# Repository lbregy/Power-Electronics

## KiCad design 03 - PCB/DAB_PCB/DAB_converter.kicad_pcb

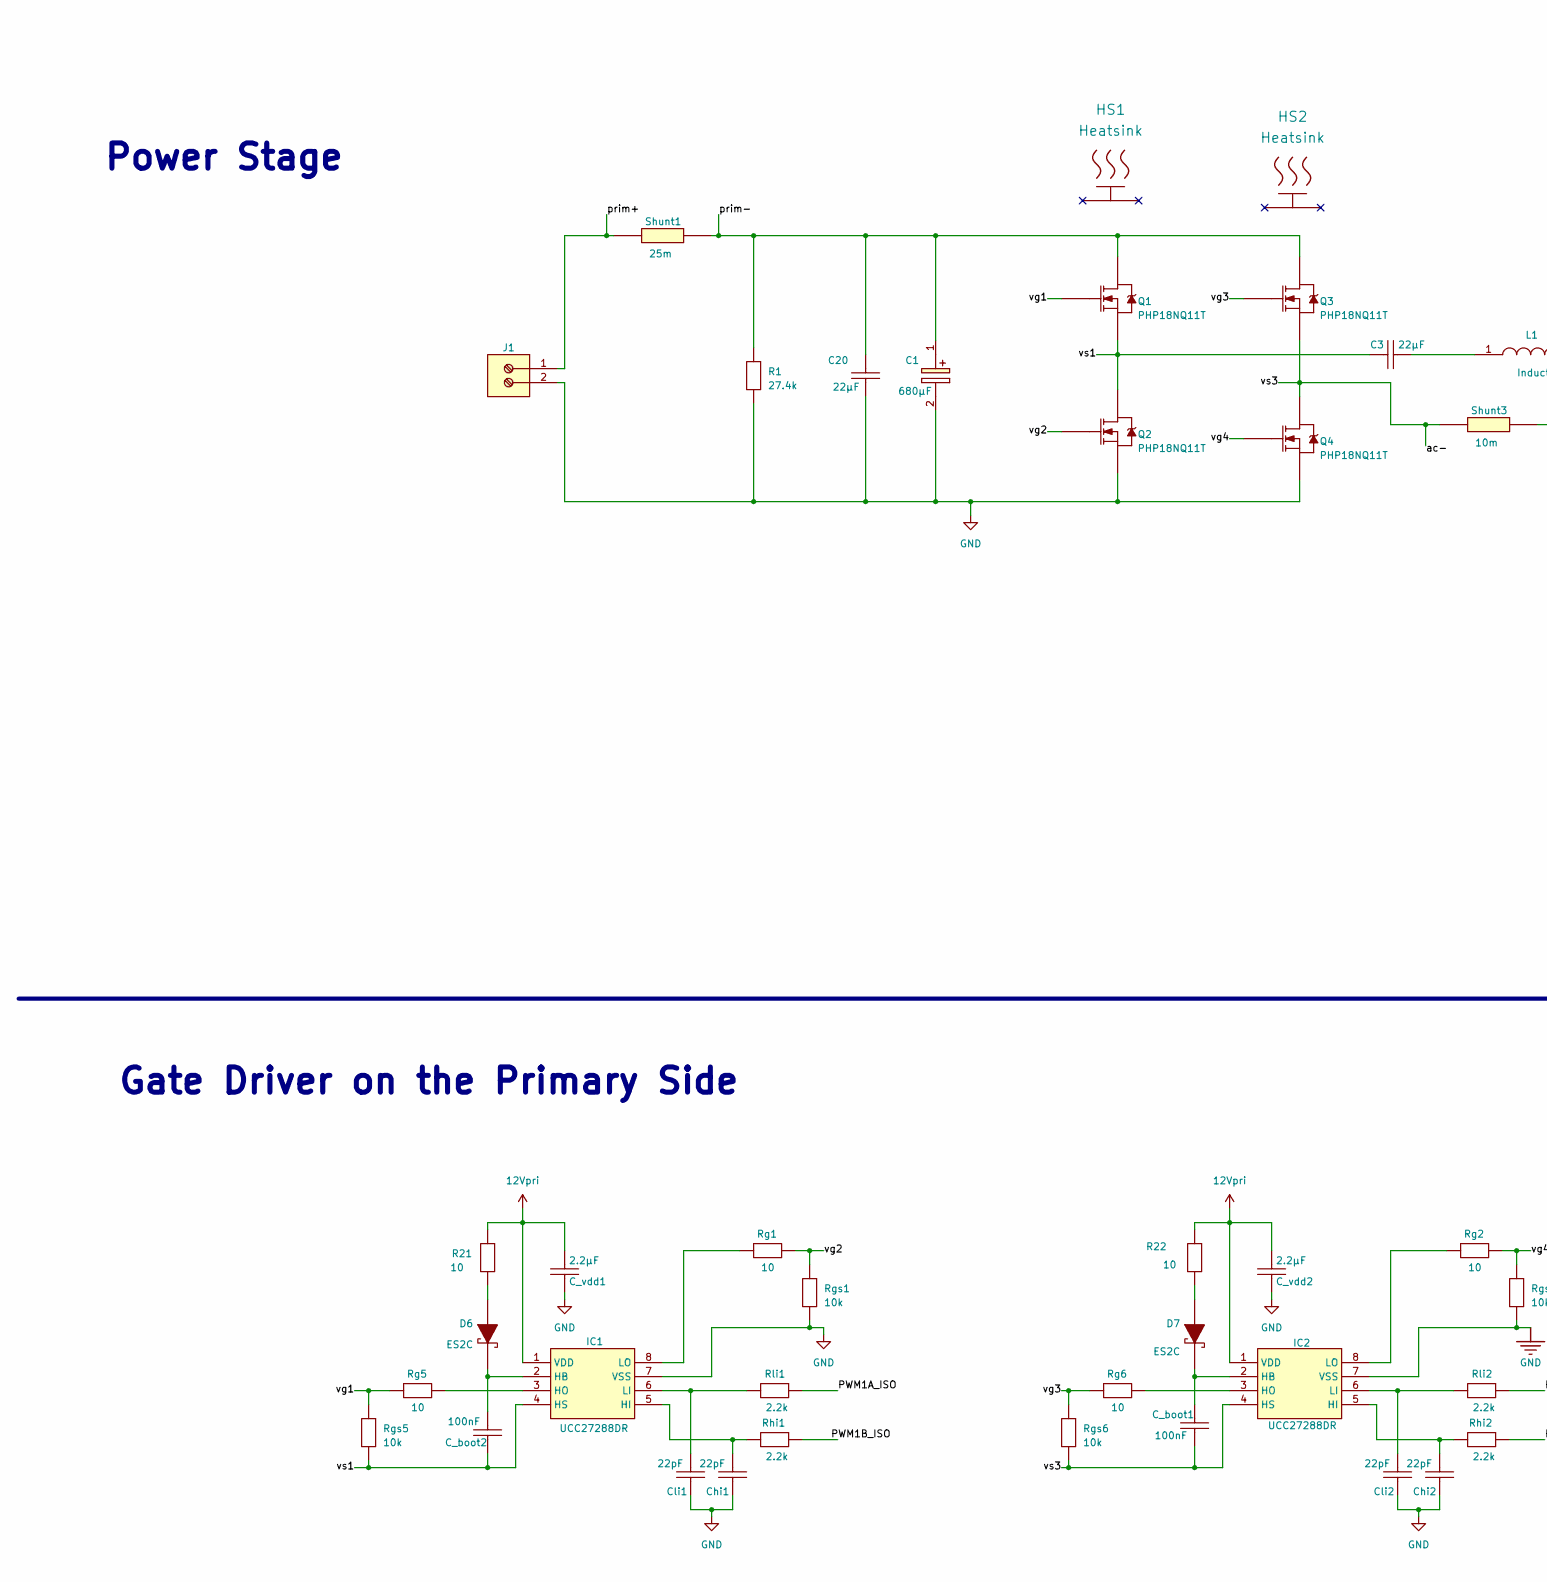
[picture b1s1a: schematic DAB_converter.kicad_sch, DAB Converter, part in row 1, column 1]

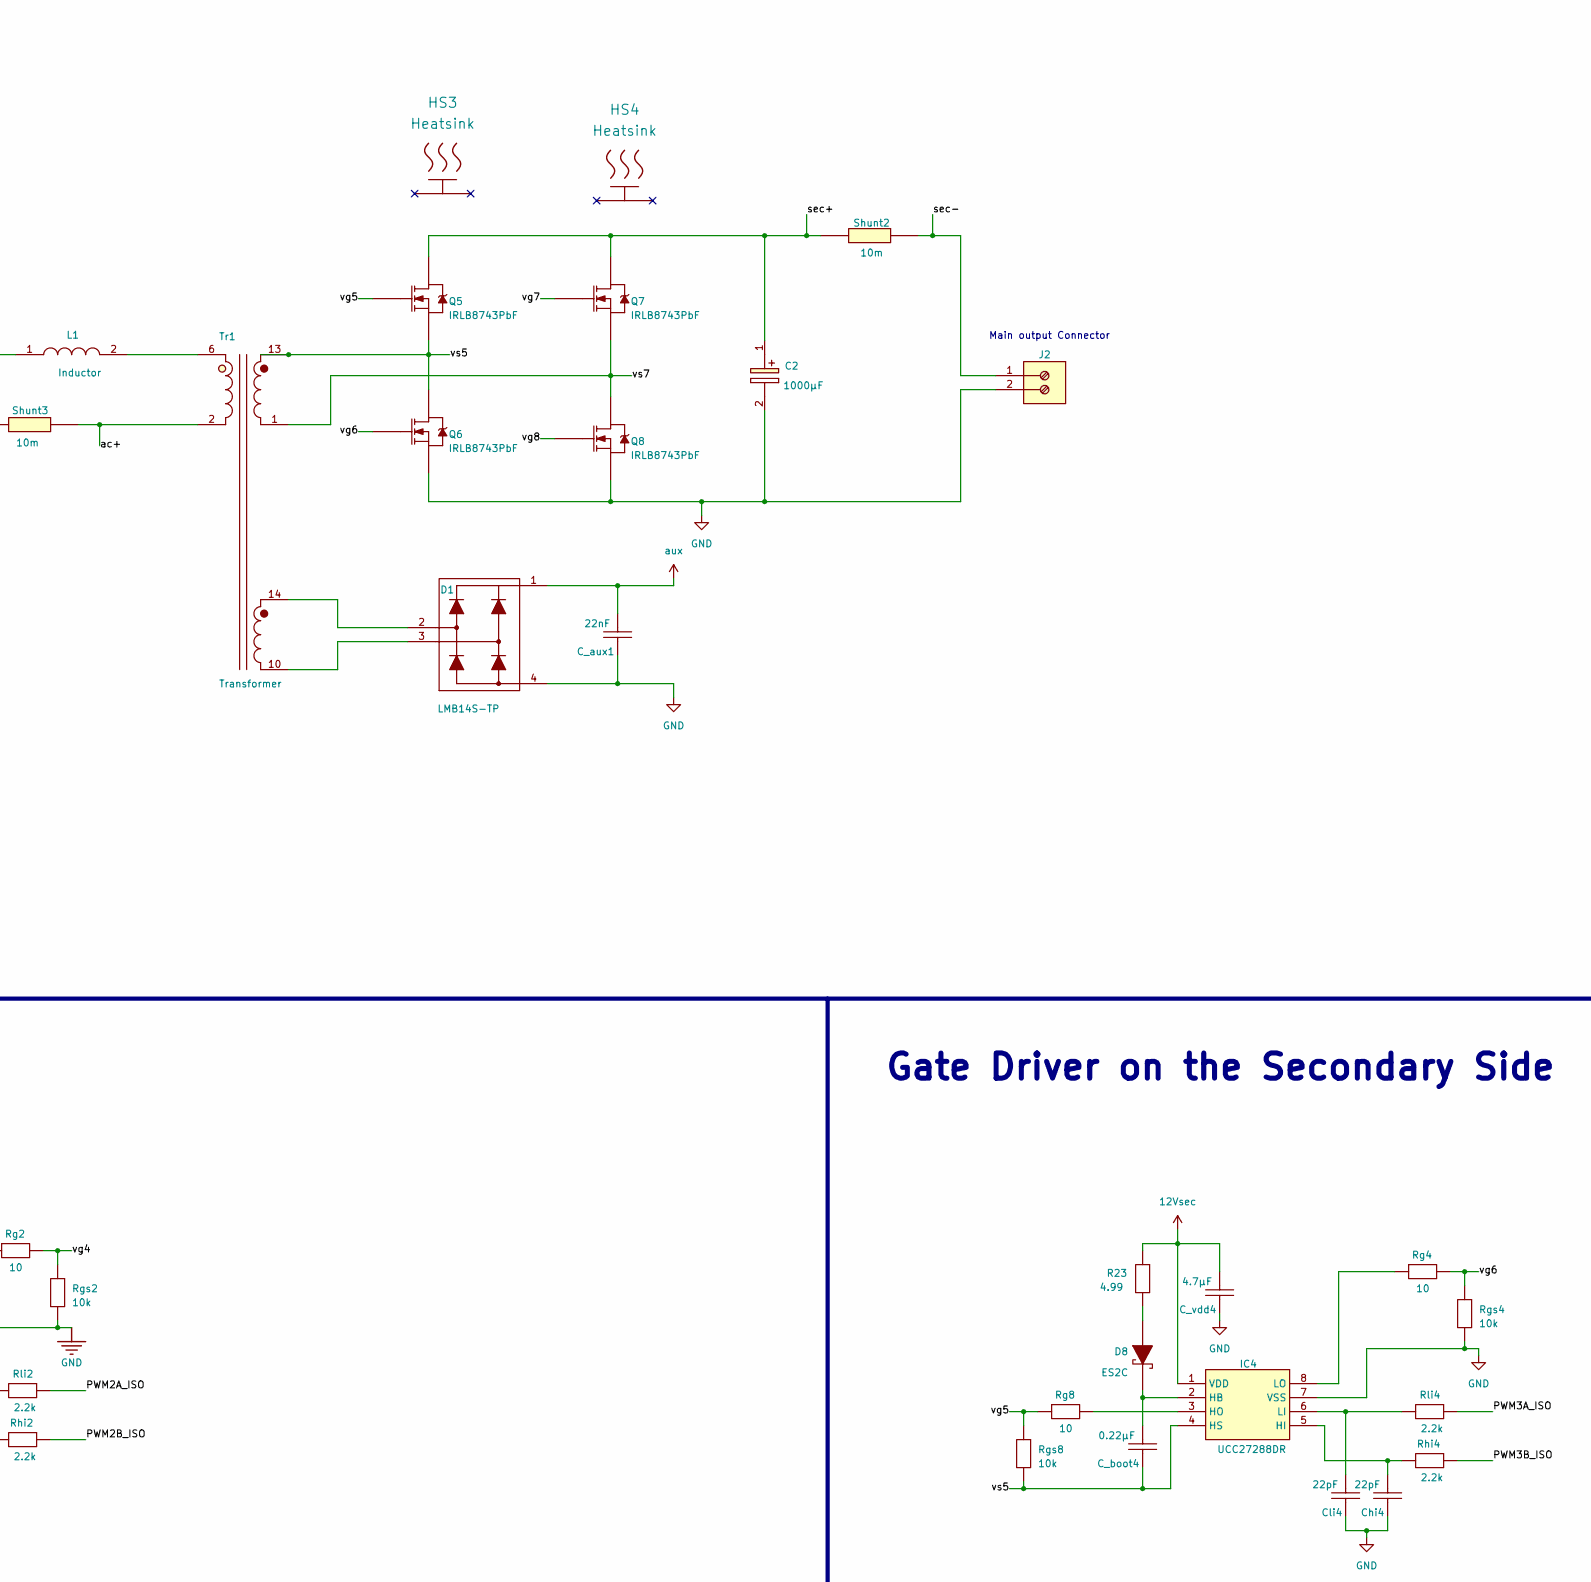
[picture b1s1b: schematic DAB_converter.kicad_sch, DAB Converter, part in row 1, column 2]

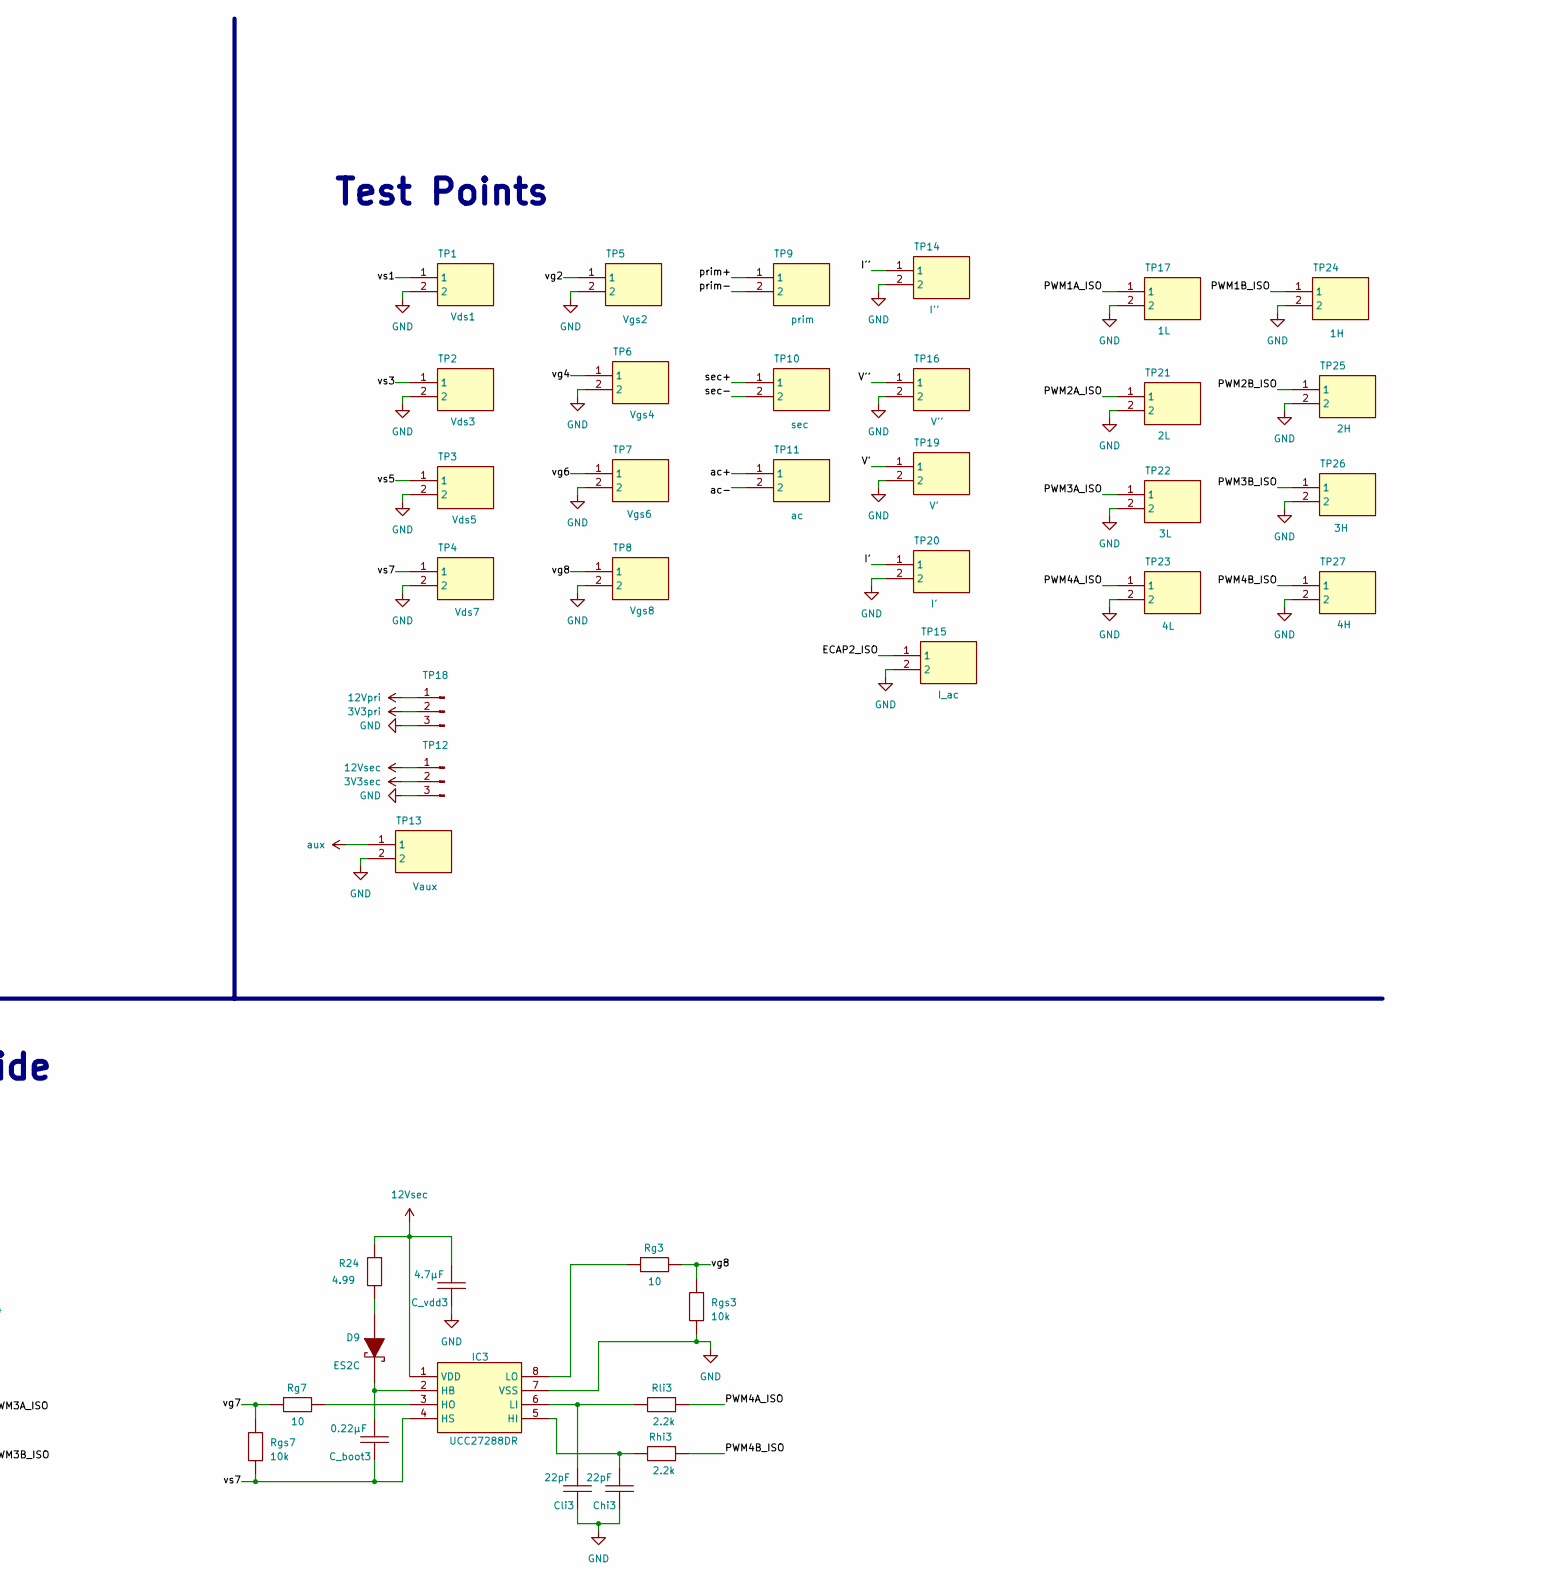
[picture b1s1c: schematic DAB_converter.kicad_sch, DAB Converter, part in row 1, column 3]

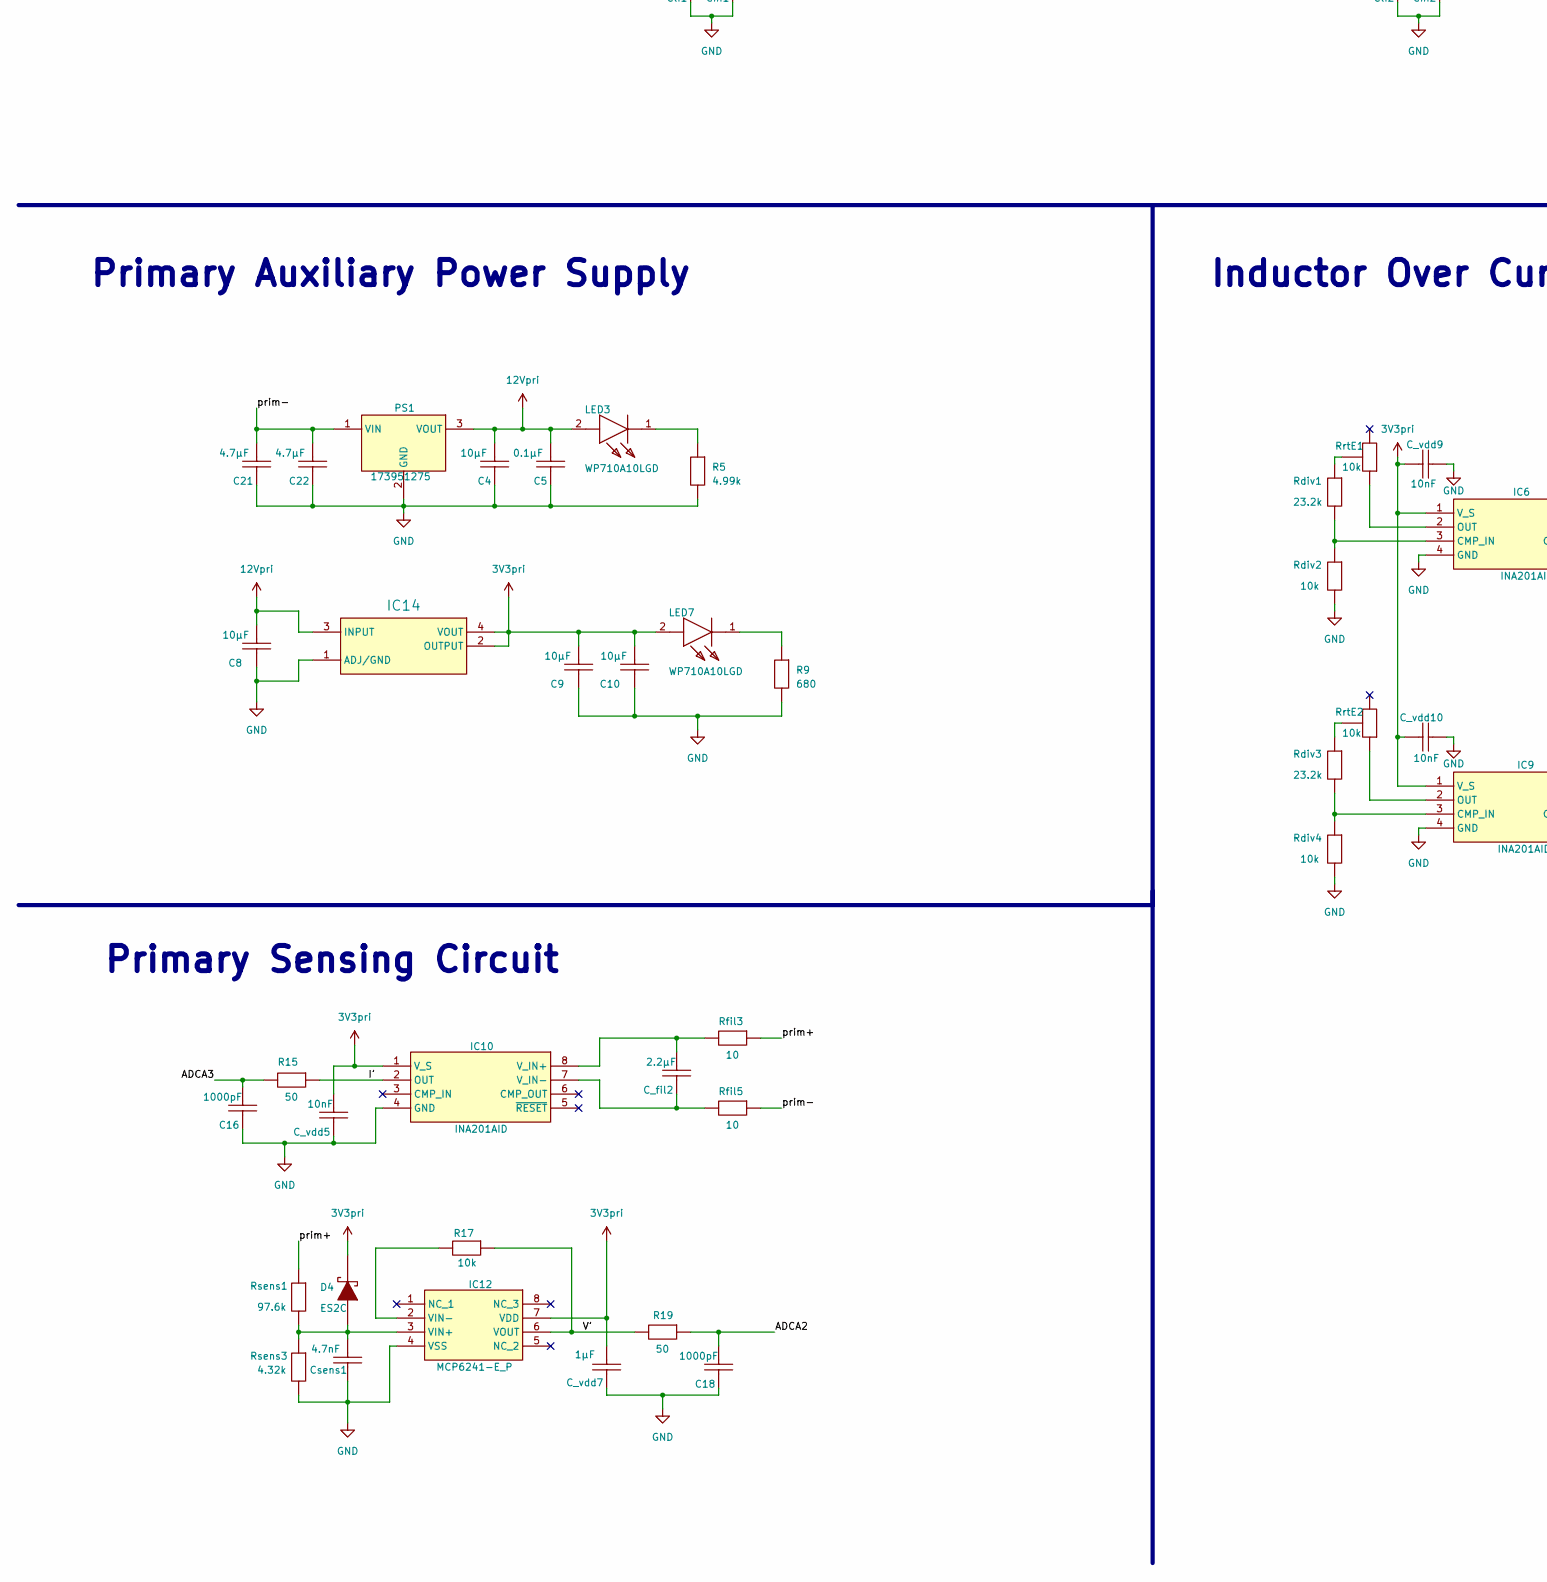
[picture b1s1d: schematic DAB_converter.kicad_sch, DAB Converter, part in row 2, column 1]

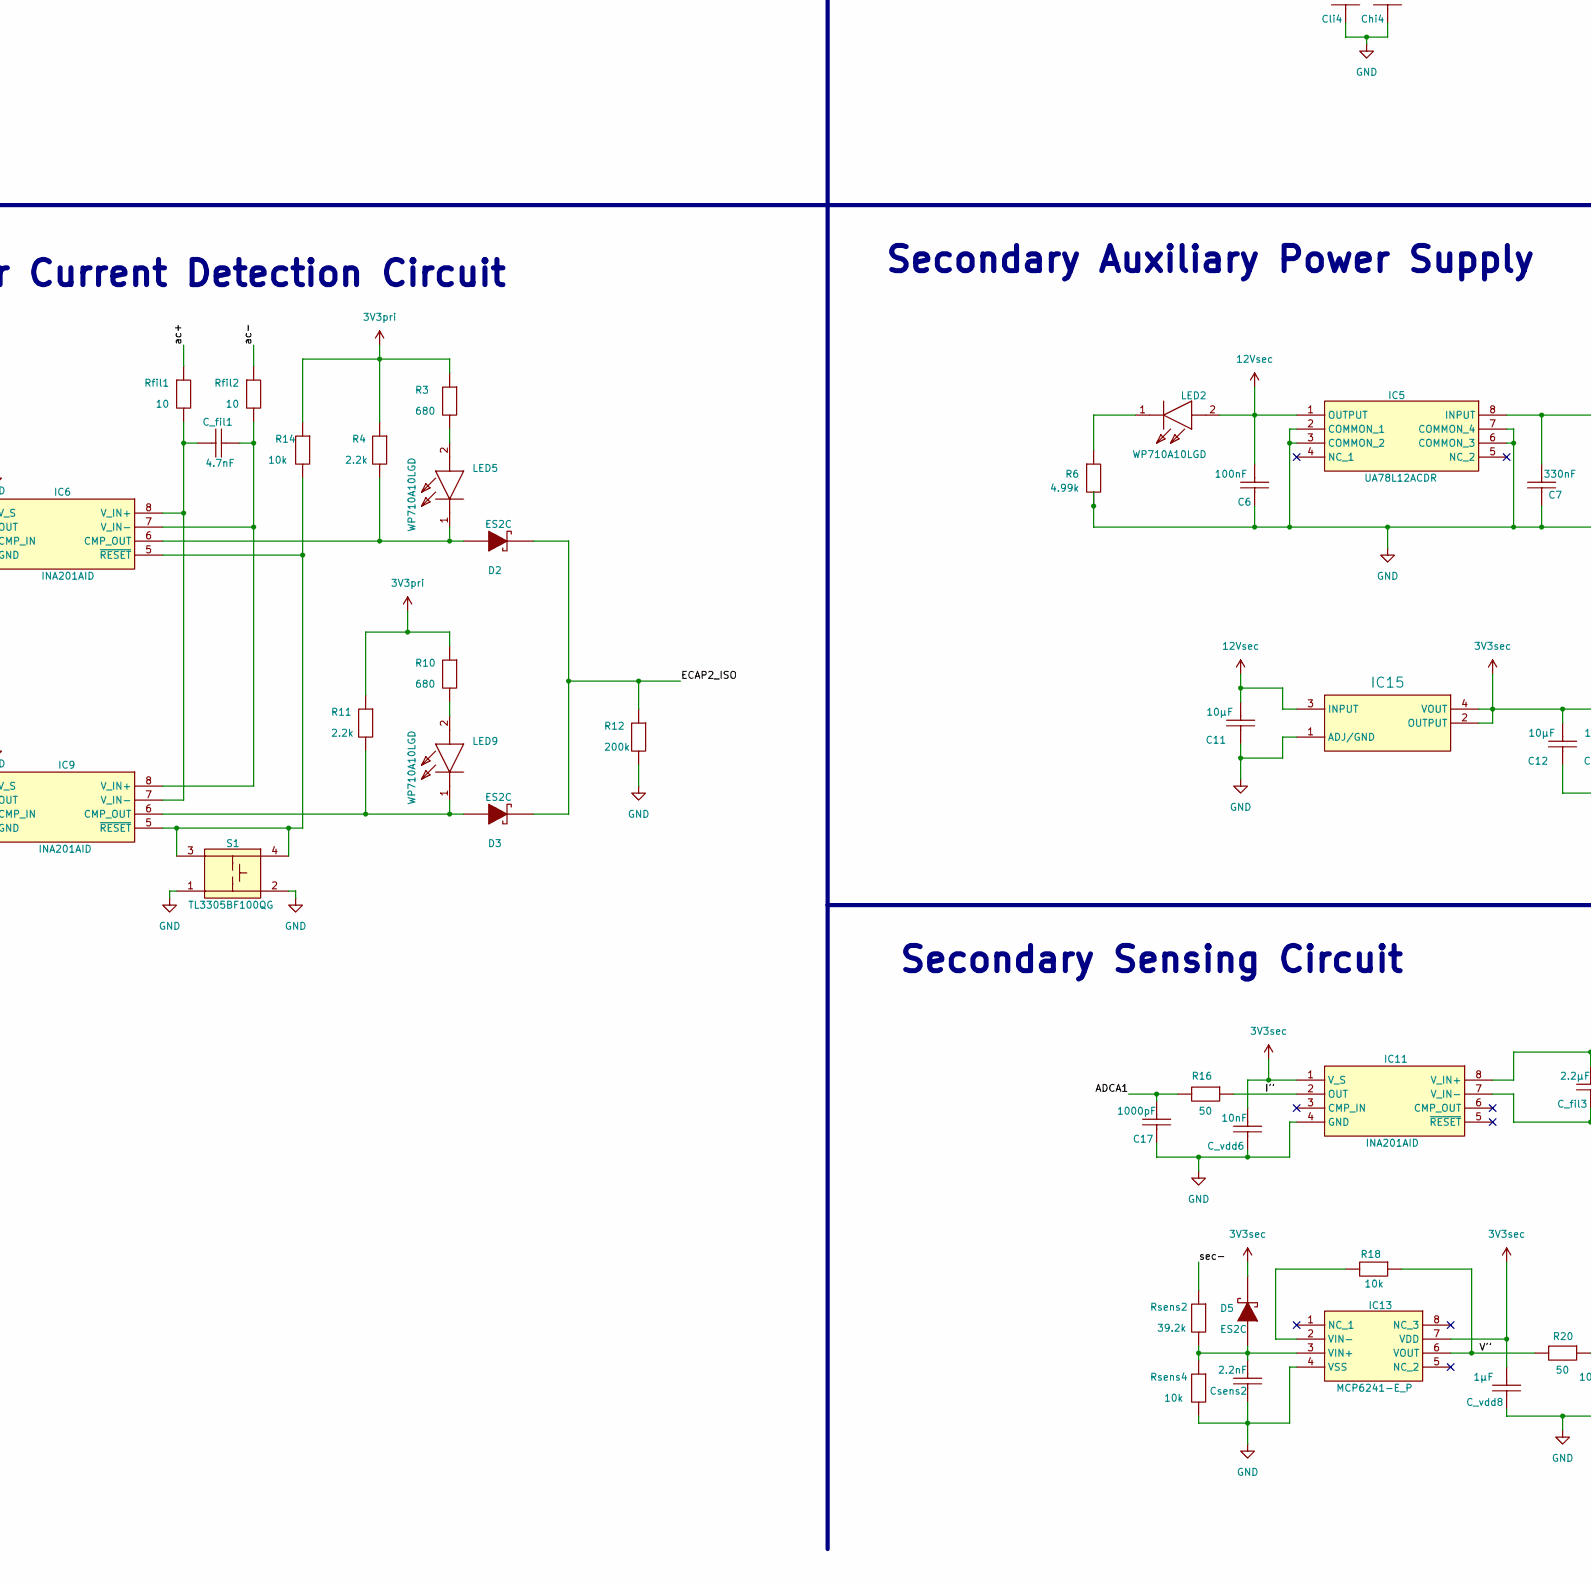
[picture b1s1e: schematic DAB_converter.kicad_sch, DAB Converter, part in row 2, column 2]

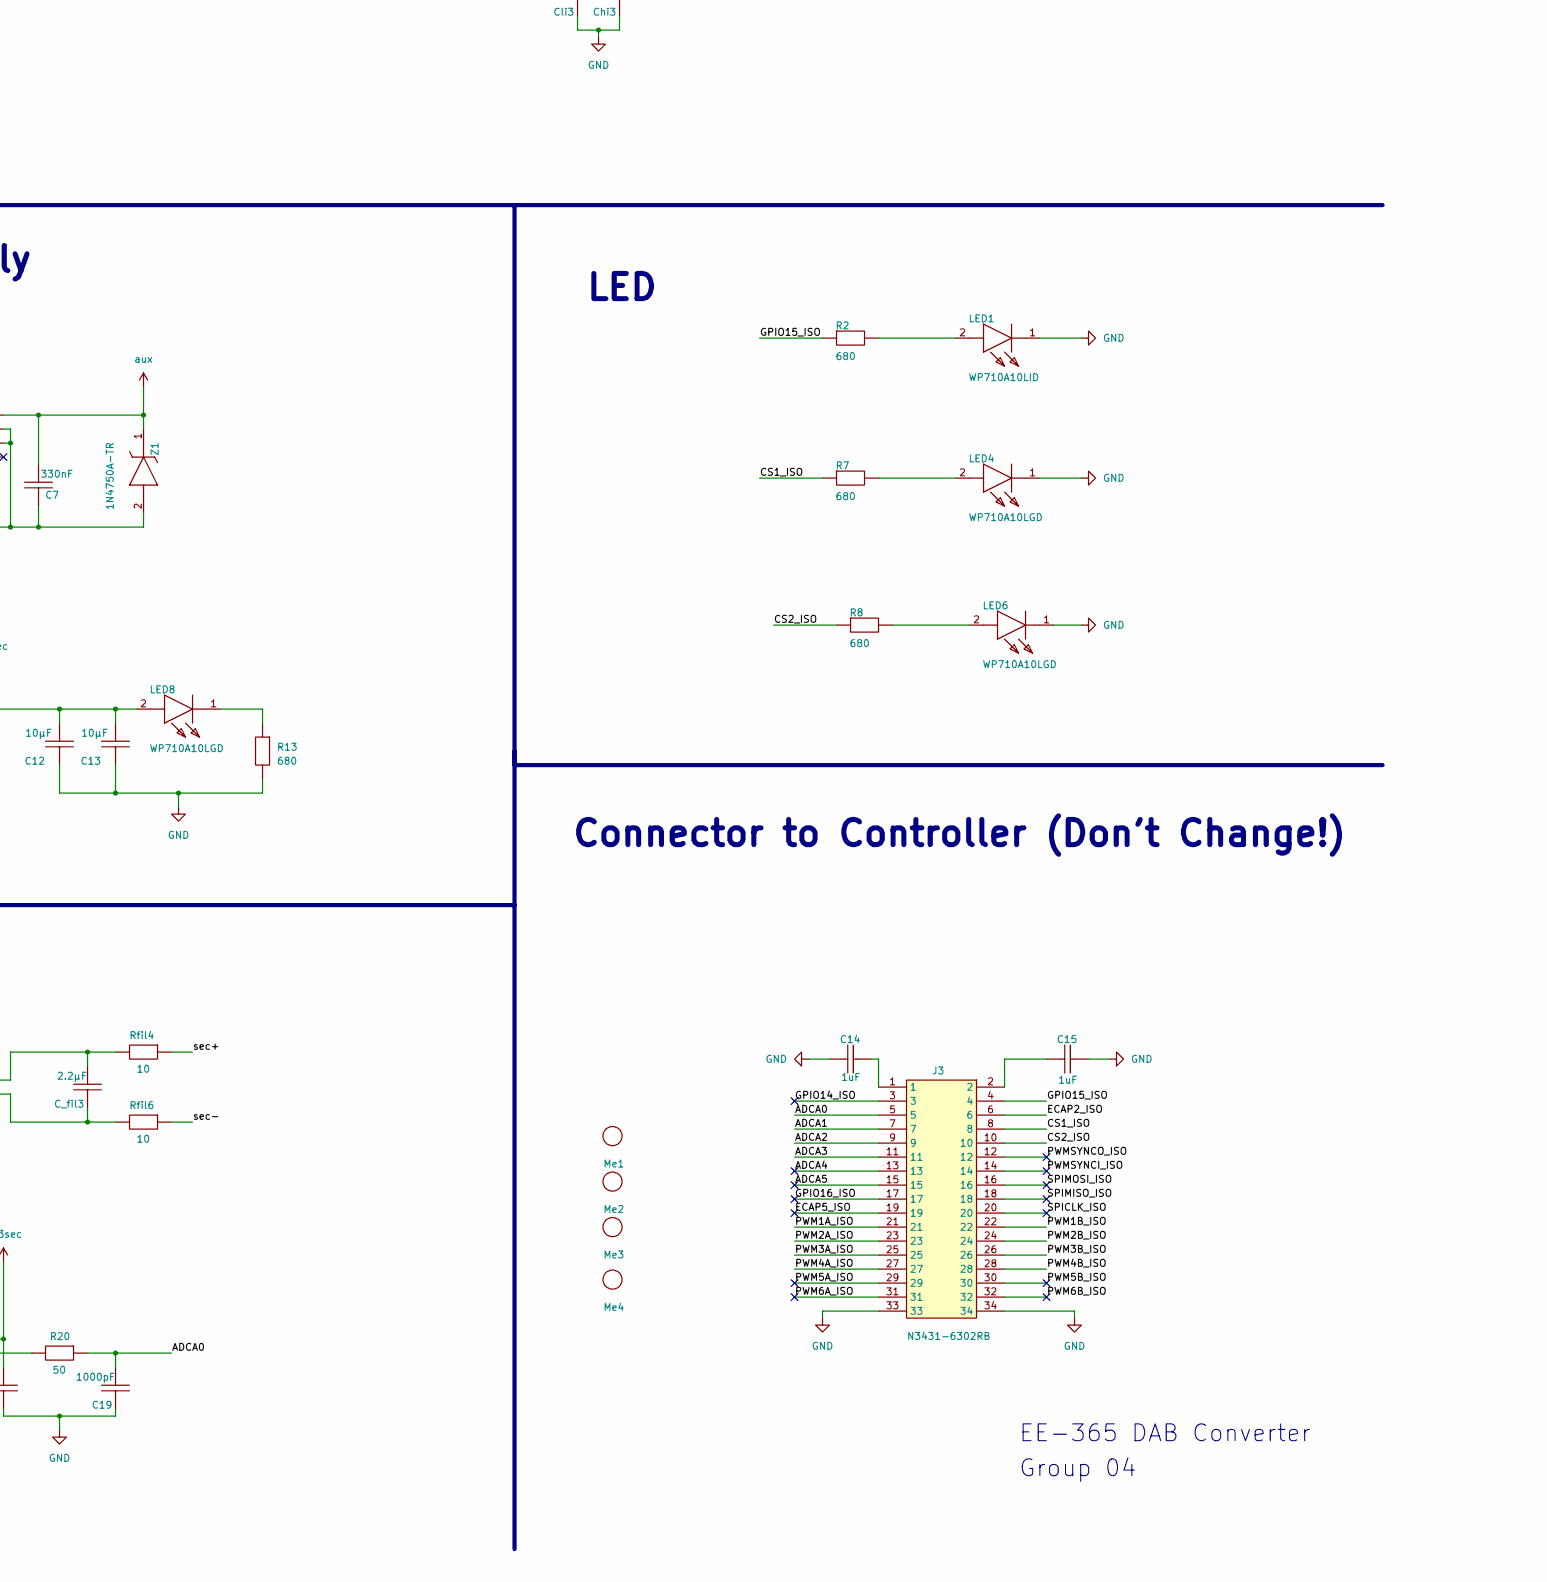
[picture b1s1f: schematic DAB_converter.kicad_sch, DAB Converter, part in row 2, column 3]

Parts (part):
C1: 680µF; CAPPRD750W80D1625H3750; MANUFACTURER_PART_NUMBER UHW2A681MHD; MOUSER PART NUMBER 647-UHW2A681MHD
C2: 1000µF; MAL215097614E3; MANUFACTURER_PART_NUMBER MAL215097614E3; MOUSER PART NUMBER 594-MAL215097614E3
C3: 22µF; C_2220_5750Metric; PART NUMBER C5750X7S2A226M280KB
C4, C8, C9, C10, C11, C12, C13: 10µF; C_1206_3216Metric
C5: 0.1µF; C_1206_3216Metric
C6: 100nF; C_1206_3216Metric
C7: 330nF; C_1206_3216Metric
C14, C15: 1uF; R_1206_3216Metric
C16, C17, C18, C19: 1000pF; C_1206_3216Metric
C20: 22µF; C_2220_5750Metric; PART NUMBER C1206C475K3PACTU
C21, C22: 4.7µF; C_1206_3216Metric; PART NUMBER GRM31CZ72A475KE1
C_aux1: 22nF; C_2220_5750Metric; PART NUMBER C5750X7S2A226M280KB
C_boot1, C_boot2: 100nF; C_1206_3216Metric; PART NUMBER C1206C224K5RACTU
C_boot3, C_boot4: 0.22µF; C_1206_3216Metric
C_fil1: 4.7nF; C_1206_3216Metric
C_fil2, C_fil3: 2.2µF; C_1206_3216Metric
C_vdd1, C_vdd2: 2.2µF; C_1206_3216Metric; PART NUMBER C1206C475K3PACTU
C_vdd3, C_vdd4: 4.7µF; C_1206_3216Metric
C_vdd5, C_vdd6, C_vdd9, C_vdd10: 10nF; C_1206_3216Metric
C_vdd7, C_vdd8: 1µF; C_1206_3216Metric
Chi1, Chi2, Chi3, Chi4: 22pF; C_1206_3216Metric
Cli1, Cli2, Cli3, Cli4: 22pF; C_1206_3216Metric
Csens1: 4.7nF; C_1206_3216Metric
Csens2: 2.2nF; C_1206_3216Metric
D1: LMB14S-TP; LMB14STP; MANUFACTURER_PART_NUMBER LMB14S-TP; MOUSER PART NUMBER 833-LMB14S-TP
D2, D3, D4, D5, D6, D7, D8, D9: ES2C; DIOM5436X244N
HS1, HS2, HS3, HS4: Heatsink; FAT22025E
IC1, IC2, IC3, IC4: UCC27288DR; SOIC127P600X175-8N; MANUFACTURER_PART_NUMBER UCC27288DR; MOUSER PART NUMBER 595-UCC27288DR
IC5: UA78L12ACDR; SOIC127P600X175-8N; MANUFACTURER_PART_NUMBER UA78L12ACDR; MOUSER PART NUMBER 595-UA78L12ACDR
IC6, IC9, IC10, IC11: INA201AID; SOIC127P600X175-8N; MANUFACTURER_PART_NUMBER INA201AID; MOUSER PART NUMBER 595-INA201AID
IC12, IC13: MCP6241-E_P; DIP781W56P254L950H533Q8N; MANUFACTURER_PART_NUMBER MCP6241-E/P; MOUSER PART NUMBER 579-MCP6241-E/P
IC14, IC15: SOT230P700X180-4N; Manufacturer_Part_Number AZ1117IH-3.3TRG1; Mouser Part Number 621-AZ1117IH-3.3TRG1
J1, J2: PHOENIX 1755736
J3: N3431-6302RB; 3M_N3431-6302RB; MANUFACTURER_PART_NUMBER HIF3FC-34PA-2.54DS(71); MOUSER PART NUMBER 798-HIF3FC34PA254DS1
L1: Inductor; inductor; MANUFACTURER_PART_NUMBER MLZ2012N100LT000; MOUSER PART NUMBER 810-MLZ2012N100LT000
LED1: WP710A10LID; MANUFACTURER_PART_NUMBER WP710A10LID; MOUSER PART NUMBER 604-WP710A10LID
LED2, LED3, LED4, LED5, LED6, LED7, LED8, LED9: WP710A10LGD; WP710A10LID; MANUFACTURER_PART_NUMBER WP710A10LGD; MOUSER PART NUMBER 604-WP710A10LGD
Me1, Me2, Me3, Me4: M3-Hole; MountingHole_3.2mm_M3
PS1: 173951275; MANUFACTURER_PART_NUMBER 173951275
Q1, Q2, Q3, Q4: PHP18NQ11T; TO-220AB
Q5, Q6, Q7, Q8: IRLB8743PbF; TO-220AB
R1: 27.4k; R_1206_3216Metric
R2, R3, R7, R8, R9, R10, R13: 680; R_1206_3216Metric
R4, R11: 2.2k; R_1206_3216Metric
R5, R6: 4.99k; R_1206_3216Metric
R12: 200k; R_1206_3216Metric
R14, R17, R18: 10k; R_1206_3216Metric
R15, R16, R19, R20: 50; R_1206_3216Metric
R21, R22: 10; R_1206_3216Metric
R23, R24: 4.99; R_1206_3216Metric
Rdiv1, Rdiv3: 23.2k; R_1206_3216Metric
Rdiv2, Rdiv4: 10k; R_1206_3216Metric
Rfil1, Rfil2, Rfil3, Rfil4, Rfil5, Rfil6: 10; R_1206_3216Metric
Rg1, Rg2, Rg3, Rg4, Rg5, Rg6, Rg7, Rg8: 10; R_1206_3216Metric
Rgs1, Rgs2, Rgs3, Rgs4, Rgs5, Rgs6, Rgs7, Rgs8: 10k; R_1206_3216Metric
Rhi1, Rhi2, Rhi3, Rhi4: 2.2k; R_1206_3216Metric
Rli1, Rli2, Rli3, Rli4: 2.2k; R_1206_3216Metric
RrtE1, RrtE2: 10k; TRIMMER CT-6EP
Rsens1: 97.6k; R_1206_3216Metric
Rsens2: 39.2k; R_1206_3216Metric
Rsens3: 4.32k; R_1206_3216Metric
Rsens4: 10k; R_1206_3216Metric
S1: TL3305BF100QG; TL3305BF160QG; MANUFACTURER_PART_NUMBER TL3305BF100QG; MOUSER PART NUMBER 612-TL3305BF100QG
Shunt1: 25m; R_2512_6332Metric; MANUFACTURER_PART_NUMBER CSNL2512FT5L00
Shunt2, Shunt3: 10m; R_2512_6332Metric; MANUFACTURER_PART_NUMBER CSNL2512FT5L00
TP1: Vds1; test point 2; MANUFACTURER_PART_NUMBER TSW-202-07-T-S; MOUSER PART NUMBER 200-TSW20207TS
TP2: Vds3; test point 2; MANUFACTURER_PART_NUMBER TSW-202-07-T-S; MOUSER PART NUMBER 200-TSW20207TS
TP3: Vds5; test point 2; MANUFACTURER_PART_NUMBER TSW-202-07-T-S; MOUSER PART NUMBER 200-TSW20207TS
TP4: Vds7; test point 2; MANUFACTURER_PART_NUMBER TSW-202-07-T-S; MOUSER PART NUMBER 200-TSW20207TS
TP5: Vgs2; test point 2; MANUFACTURER_PART_NUMBER TSW-202-07-T-S; MOUSER PART NUMBER 200-TSW20207TS
TP6: Vgs4; test point 2; MANUFACTURER_PART_NUMBER TSW-202-07-T-S; MOUSER PART NUMBER 200-TSW20207TS
TP7: Vgs6; test point 2; MANUFACTURER_PART_NUMBER TSW-202-07-T-S; MOUSER PART NUMBER 200-TSW20207TS
TP8: Vgs8; test point 2; MANUFACTURER_PART_NUMBER TSW-202-07-T-S; MOUSER PART NUMBER 200-TSW20207TS
TP9: prim; test point 2; MANUFACTURER_PART_NUMBER TSW-202-07-T-S; MOUSER PART NUMBER 200-TSW20207TS
TP10: sec; test point 2; MANUFACTURER_PART_NUMBER TSW-202-07-T-S; MOUSER PART NUMBER 200-TSW20207TS
TP11: ac; test point 2; MANUFACTURER_PART_NUMBER TSW-202-07-T-S; MOUSER PART NUMBER 200-TSW20207TS
TP12, TP18: TP?; PinHeader_1x03_P2.54mm_Vertical
TP13: Vaux; test point 2; MANUFACTURER_PART_NUMBER TSW-202-07-T-S; MOUSER PART NUMBER 200-TSW20207TS
TP14: I''; test point 2; MANUFACTURER_PART_NUMBER TSW-202-07-T-S; MOUSER PART NUMBER 200-TSW20207TS
TP15: I_ac; test point 2; MANUFACTURER_PART_NUMBER TSW-202-07-T-S; MOUSER PART NUMBER 200-TSW20207TS
TP16: V''; test point 2; MANUFACTURER_PART_NUMBER TSW-202-07-T-S; MOUSER PART NUMBER 200-TSW20207TS
TP17: 1L; test point 2; MANUFACTURER_PART_NUMBER TSW-202-07-T-S; MOUSER PART NUMBER 200-TSW20207TS
TP19: V'; test point 2; MANUFACTURER_PART_NUMBER TSW-202-07-T-S; MOUSER PART NUMBER 200-TSW20207TS
TP20: I'; test point 2; MANUFACTURER_PART_NUMBER TSW-202-07-T-S; MOUSER PART NUMBER 200-TSW20207TS
TP21: 2L; test point 2; MANUFACTURER_PART_NUMBER TSW-202-07-T-S; MOUSER PART NUMBER 200-TSW20207TS
TP22: 3L; test point 2; MANUFACTURER_PART_NUMBER TSW-202-07-T-S; MOUSER PART NUMBER 200-TSW20207TS
TP23: 4L; test point 2; MANUFACTURER_PART_NUMBER TSW-202-07-T-S; MOUSER PART NUMBER 200-TSW20207TS
TP24: 1H; test point 2; MANUFACTURER_PART_NUMBER TSW-202-07-T-S; MOUSER PART NUMBER 200-TSW20207TS
TP25: 2H; test point 2; MANUFACTURER_PART_NUMBER TSW-202-07-T-S; MOUSER PART NUMBER 200-TSW20207TS
TP26: 3H; test point 2; MANUFACTURER_PART_NUMBER TSW-202-07-T-S; MOUSER PART NUMBER 200-TSW20207TS
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
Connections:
3V3pri: C9.2, C10.2, C_vdd5.2, C_vdd7.2, C_vdd9.2, C_vdd10.2, D4.1 (K), IC6.1 (V_S), IC9.1 (V_S), IC10.1 (V_S), IC12.7 (VDD), IC14.2 (OUTPUT), IC14.4 (VOUT), LED7.2 (A), R3.2, R4.2, R10.2, R11.2, R14.2, TP18.2
3V3sec: C12.2, C13.2, C_vdd6.2, C_vdd8.2, D5.1 (K), IC11.1 (V_S), IC13.7 (VDD), IC15.2 (OUTPUT), IC15.4 (VOUT), LED8.2 (A), TP12.2
12Vpri: C4.2, C5.2, C8.2, C_vdd1.2, C_vdd2.2, IC1.1 (VDD), IC2.1 (VDD), IC14.3 (INPUT), LED3.2 (A), PS1.3 (VOUT), R21.2, R22.2, TP18.1
12Vsec: C6.2, C11.2, C_vdd3.2, C_vdd4.2, IC3.1 (VDD), IC4.1 (VDD), IC5.1 (OUTPUT), IC15.3 (INPUT), LED2.2 (A), R23.2, R24.2, TP12.1
/ADCA0: C19.2, J3.5, R20.2
/ADCA1: C17.2, J3.7, R16.1
/ADCA2: C18.2, J3.9, R19.2
/ADCA3: C16.2, J3.11, R15.1
/ADCA4: J3.13
/ADCA5: J3.15
/CS1_ISO: J3.8, R7.2
/CS2_ISO: J3.10, R8.2
/ECAP2_ISO: D2.1 (K), D3.1 (K), J3.6, R12.2, TP15.1
/ECAP5_ISO: J3.19
/GPIO14_ISO: J3.3
/GPIO15_ISO: J3.4, R2.2
/GPIO16_ISO: J3.17
/I': IC10.2 (OUT), R15.2, TP20.1
/I'': IC11.2 (OUT), R16.2, TP14.1
/PWM1A_ISO: J3.21, Rli1.2, TP17.1
/PWM1B_ISO: J3.22, Rhi1.2, TP24.1
/PWM2A_ISO: J3.23, Rli2.2, TP21.1
/PWM2B_ISO: J3.24, Rhi2.2, TP25.1
/PWM3A_ISO: J3.25, Rli4.2, TP22.1
/PWM3B_ISO: J3.26, Rhi4.2, TP26.1
/PWM4A_ISO: J3.27, Rli3.2, TP23.1
/PWM4B_ISO: J3.28, Rhi3.2, TP27.1
/PWM5A_ISO: J3.29
/PWM5B_ISO: J3.30
/PWM6A_ISO: J3.31
/PWM6B_ISO: J3.32
/PWMSYNCI_ISO: J3.14
/PWMSYNCO_ISO: J3.12
/SPICLK_ISO: J3.20
/SPIMISO_ISO: J3.18
/SPIMOSI_ISO: J3.16
/V': IC12.6 (VOUT), R17.2, R19.1, TP19.1
/V'': IC13.6 (VOUT), R18.2, R20.1, TP16.1
/ac+: Rfil1.2, Shunt3.2, TP11.1, Tr1.2
/ac-: C_boot1.1, IC2.4 (HS), Q3.3 (S), Q4.2 (D), Rfil2.2, Rgs6.1, Shunt3.1, TP2.1, TP11.2
/prim+: J1.1, Rfil3.2, Rsens1.2, Shunt1.1, TP9.1
/prim-: C1.1 (+), C20.2, C21.2, C22.2, PS1.1 (VIN), Q1.2 (D), Q3.2 (D), R1.2, Rfil5.2, Shunt1.2, TP9.2
/sec+: C2.1 (+), Q5.2 (D), Q7.2 (D), Rfil4.2, Shunt2.1, TP10.1
/sec-: J2.1, Rfil6.2, Rsens2.2, Shunt2.2, TP10.2
/vg1: Q1.1 (G), Rg5.2, Rgs5.2
/vg2: Q2.1 (G), Rg1.1, Rgs1.2, TP5.1
/vg3: Q3.1 (G), Rg6.2, Rgs6.2
/vg4: Q4.1 (G), Rg2.1, Rgs2.2, TP6.1
/vg5: Q5.1 (G), Rg8.2, Rgs8.2
/vg6: Q6.1 (G), Rg4.1, Rgs4.2, TP7.1
/vg7: Q7.1 (G), Rg7.2, Rgs7.2
/vg8: Q8.1 (G), Rg3.1, Rgs3.2, TP8.1
/vs1: C3.1, C_boot2.1, IC1.4 (HS), Q1.3 (S), Q2.2 (D), Rgs5.1, TP1.1
/vs5: C_boot4.1, IC4.4 (HS), Q5.3 (S), Q6.2 (D), Rgs8.1, TP3.1, Tr1.13 (1)
/vs7: C_boot3.1, IC3.4 (HS), Q7.3 (S), Q8.2 (D), Rgs7.1, TP4.1, Tr1.1
GND: C1.2 (-), C2.2 (-), C4.1, C5.1, C6.1, C7.1, C8.1, C9.1, C10.1, C11.1, C12.1, C13.1, C14.1, C15.2, C16.1, C17.1, C18.1, C19.1, C20.1, C21.1, C22.1, C_aux1.1, C_vdd1.1, C_vdd2.1, C_vdd3.1, C_vdd4.1, C_vdd5.1, C_vdd6.1, C_vdd7.1, C_vdd8.1, C_vdd9.1, C_vdd10.1, Chi1.1, Chi2.1, Chi3.1, Chi4.1, Cli1.1, Cli2.1, Cli3.1, Cli4.1, Csens1.1, Csens2.1, D1.4 (K), IC1.7 (VSS), IC2.7 (VSS), IC3.7 (VSS), IC4.7 (VSS), IC5.2 (COMMON_1), IC5.3 (COMMON_2), IC5.6 (COMMON_3), IC5.7 (COMMON_4), IC6.4 (GND), IC9.4 (GND), IC10.4 (GND), IC11.4 (GND), IC12.4 (VSS), IC13.4 (VSS), IC14.1 (ADJ/GND), IC15.1 (ADJ/GND), J1.2, J2.2, J3.33, J3.34, LED1.1 (K), LED4.1 (K), LED6.1 (K), PS1.2 (GND), Q2.3 (S), Q4.3 (S), Q6.3 (S), Q8.3 (S), R1.1, R5.1, R6.1, R9.1, R12.1, R13.1, Rdiv2.1, Rdiv4.1, Rgs1.1, Rgs2.1, Rgs3.1, Rgs4.1, Rsens3.1, Rsens4.1, S1.1, S1.2, TP1.2, TP2.2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
unnamed: C3.2, L1.1
unnamed: C14.2, J3.1
unnamed: C15.1, J3.2
unnamed: D1.2 (AC_1), Tr1.14
unnamed: D1.3 (AC_2), Tr1.10
unnamed: D2.2 (A), IC6.6 (CMP_OUT), LED5.1 (K), R4.1
unnamed: D3.2 (A), IC9.6 (CMP_OUT), LED9.1 (K), R11.1
unnamed: Csens1.2, D4.2 (A), IC12.3 (VIN+), Rsens1.1, Rsens3.2
unnamed: Csens2.2, D5.2 (A), IC13.3 (VIN+), Rsens2.1, Rsens4.2
unnamed: D6.2 (A), R21.1
unnamed: C_boot2.2, D6.1 (K), IC1.2 (HB)
unnamed: D7.2 (A), R22.1
unnamed: C_boot1.2, D7.1 (K), IC2.2 (HB)
unnamed: D8.2 (A), R23.1
unnamed: C_boot4.2, D8.1 (K), IC4.2 (HB)
unnamed: D9.2 (A), R24.1
unnamed: C_boot3.2, D9.1 (K), IC3.2 (HB)
unnamed: Chi1.2, IC1.5 (HI), Rhi1.1
unnamed: IC1.3 (HO), Rg5.1
unnamed: Cli1.2, IC1.6 (LI), Rli1.1
unnamed: IC1.8 (LO), Rg1.2
unnamed: Chi2.2, IC2.5 (HI), Rhi2.1
unnamed: IC2.3 (HO), Rg6.1
unnamed: Cli2.2, IC2.6 (LI), Rli2.1
unnamed: IC2.8 (LO), Rg2.2
unnamed: Chi3.2, IC3.5 (HI), Rhi3.1
unnamed: IC3.3 (HO), Rg7.1
unnamed: Cli3.2, IC3.6 (LI), Rli3.1
unnamed: IC3.8 (LO), Rg3.2
unnamed: Chi4.2, IC4.5 (HI), Rhi4.1
unnamed: IC4.3 (HO), Rg8.1
unnamed: Cli4.2, IC4.6 (LI), Rli4.1
unnamed: IC4.8 (LO), Rg4.2
unnamed: IC6.3 (CMP_IN), Rdiv1.1, Rdiv2.2
unnamed: IC6.2 (OUT), RrtE1.1
unnamed: C_fil1.2, IC6.8 (V_IN+), IC9.7 (V_IN-), Rfil1.1
unnamed: C_fil1.1, IC6.7 (V_IN-), IC9.8 (V_IN+), Rfil2.1
unnamed: IC6.5 (~RESET), IC9.5 (~RESET), R14.1, S1.3, S1.4
unnamed: IC9.3 (CMP_IN), Rdiv3.1, Rdiv4.2
unnamed: IC9.2 (OUT), RrtE2.1
unnamed: C_fil2.2, IC10.8 (V_IN+), Rfil3.1
unnamed: C_fil2.1, IC10.7 (V_IN-), Rfil5.1
unnamed: C_fil3.2, IC11.8 (V_IN+), Rfil4.1
unnamed: C_fil3.1, IC11.7 (V_IN-), Rfil6.1
unnamed: IC12.2 (VIN-), R17.1
unnamed: IC13.2 (VIN-), R18.1
unnamed: L1.2, Tr1.6
unnamed: LED1.2 (A), R2.1
unnamed: LED2.1 (K), R6.2
unnamed: LED3.1 (K), R5.2
unnamed: LED4.2 (A), R7.1
unnamed: LED5.2 (A), R3.1
unnamed: LED6.2 (A), R8.1
unnamed: LED7.1 (K), R9.2
unnamed: LED8.1 (K), R13.2
unnamed: LED9.2 (A), R10.1
unnamed: Rdiv1.2, RrtE1.2
unnamed: Rdiv3.2, RrtE2.2
aux: C7.2, C_aux1.2, D1.1 (A), IC5.8 (INPUT), TP13.1, Z1.1 (K)

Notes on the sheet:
Main output Connector
Gate Driver on the Secondary Side
EE-365 DAB Converter
Group 04
Secondary Sensing Circuit
Power Stage
Primary Auxiliary Power Supply
Primary Sensing Circuit
Gate Driver on the Primary Side
Secondary Auxiliary Power Supply
Test Points
Connector to Controller (Don't Change!)
Inductor Over Current Detection Circuit
LED

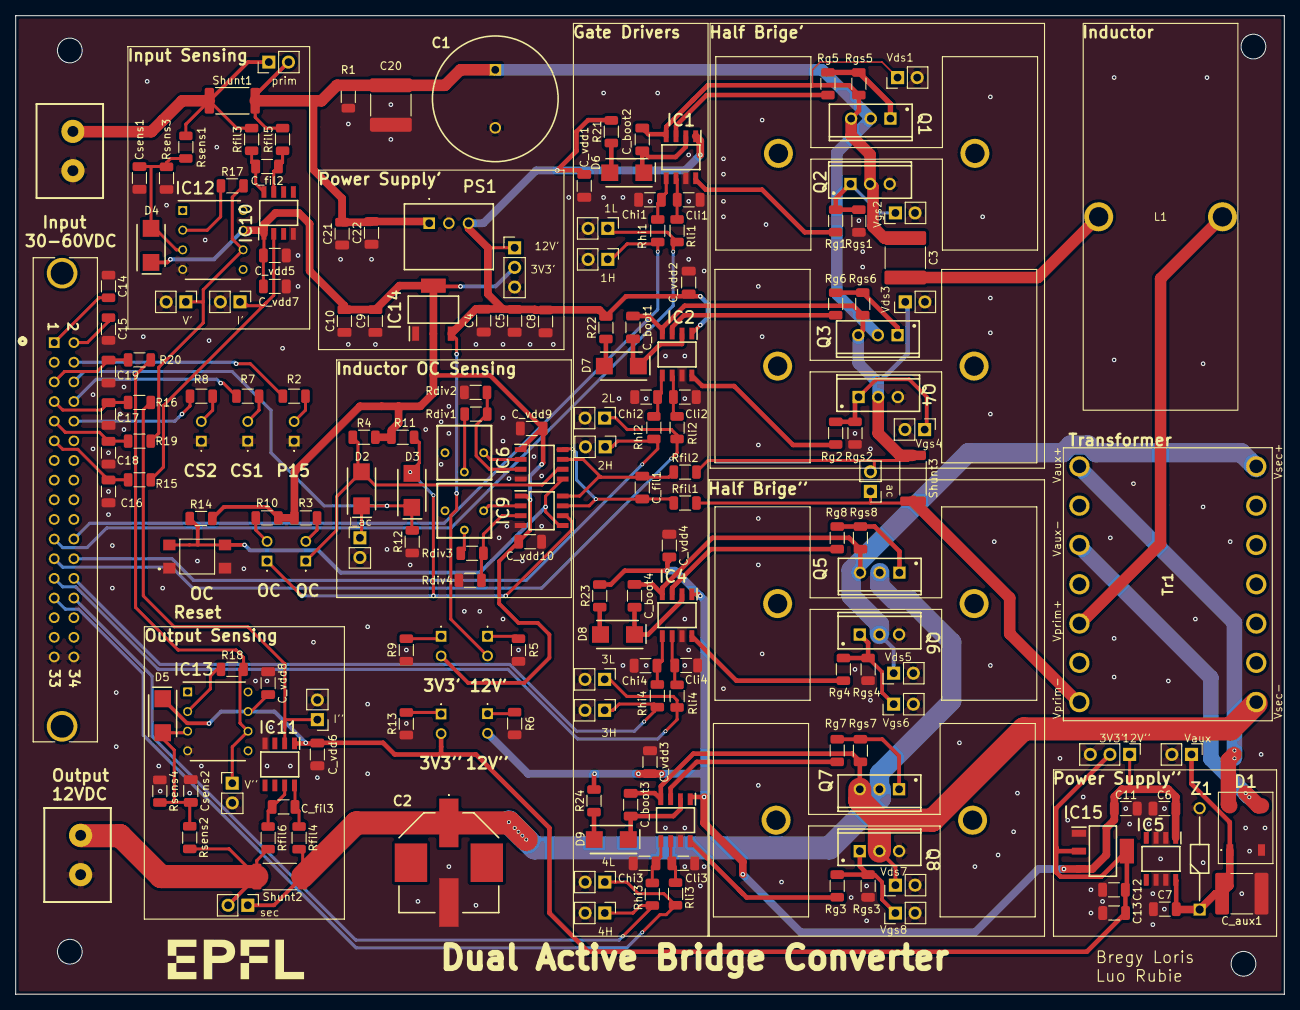
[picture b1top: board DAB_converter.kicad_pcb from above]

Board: 2 copper layers, 164.0 x 126.5 mm, 199 parts (0 on the bottom side), 101 nets.

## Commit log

2026-03-03 Inital commit
2026-03-03 Q5-Q12
2026-03-04 semic
2026-03-10 removed plecs lib
2026-03-11 matlab loses
2026-03-15 first stage swiching loss
2026-03-15 rendement
2026-03-15 heatsink
2026-03-17 mosfet singla
2026-03-17 mosfet
2026-03-17 added rapport 2
2026-03-17 q1-5
2026-03-23 correctet gitingore
2026-04-16 up to Q15
2026-04-16 fix commit and report 3
2026-04-16 upt o q40
2026-04-17 power stage + gate driver schematc
2026-04-18 power supply and measuremtents schematics
2026-04-20 correct input and output capcitors values from rapport1
2026-04-21 lined almost every footprint
2026-04-21 use fixed cap values
2026-04-21 added testpoints
2026-05-01 started routing
2026-05-01 added all test points
2026-05-01 more routing
2026-05-01 gate drivers routed
2026-05-02 DC-DC
2026-05-03 DRC passed
2026-05-03 cleaned up silkscreen
2026-05-04 added ground vias
